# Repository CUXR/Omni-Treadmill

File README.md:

# Omni-Treadmill
A device capable of detecting motion and mimicking natural movement while keeping the users static.

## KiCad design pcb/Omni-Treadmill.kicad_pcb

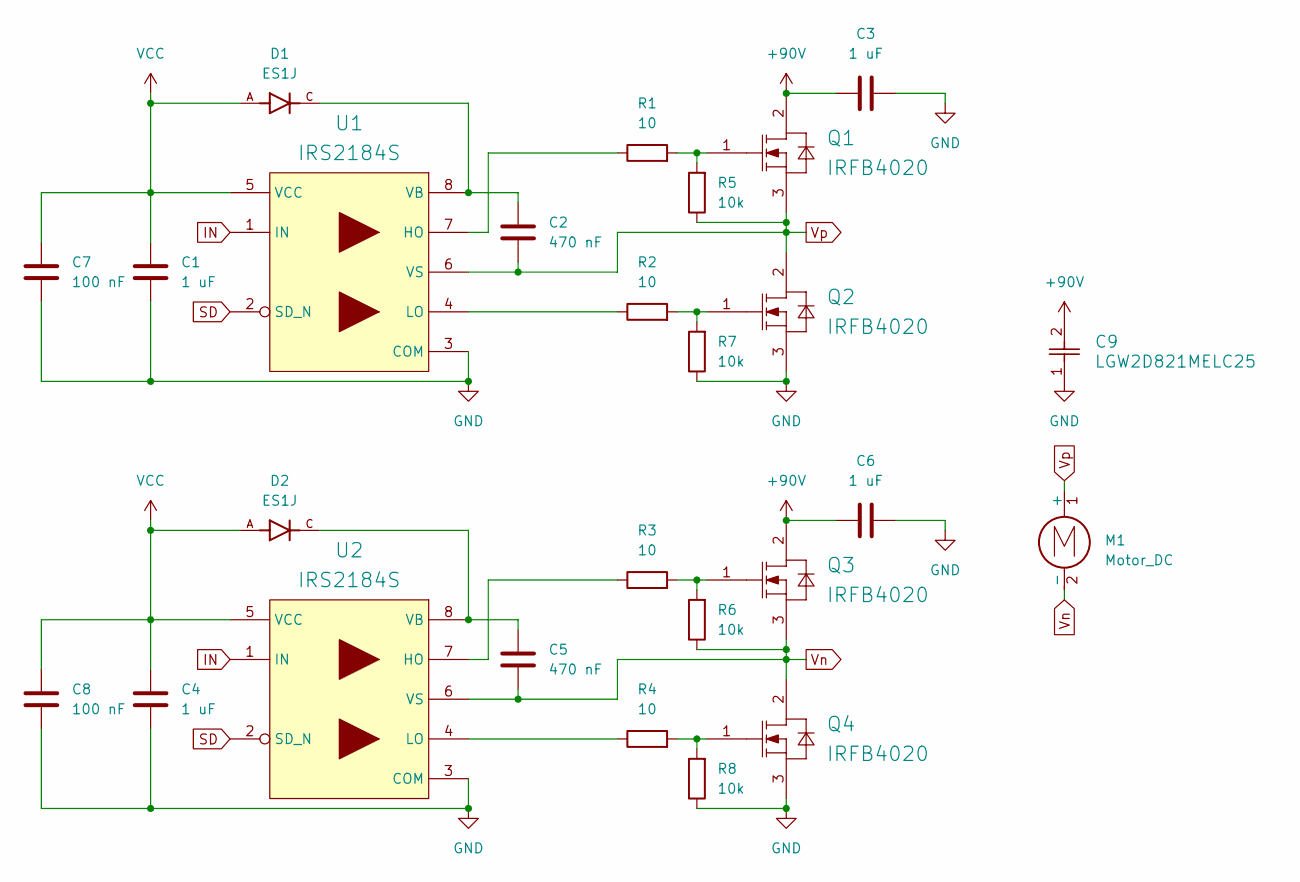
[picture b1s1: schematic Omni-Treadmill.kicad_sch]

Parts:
C1, C3, C4, C6: 1 uF; C_1812_4532Metric_Pad1.57x3.40mm_HandSolder
C2, C5: 470 nF; C_1812_4532Metric_Pad1.57x3.40mm_HandSolder
C7, C8: 100 nF; C_1206_3216Metric_Pad1.33x1.80mm_HandSolder
C9: LGW2D821MELC25; CAP_C25_NCH
D1, D2: ES1J; DIOM4325X250N; PARTREV L2102
M1: Motor_DC
Q1, Q2, Q3, Q4: IRFB4020; IFX-PG-TO220-3-904
R1, R2, R3, R4: 10; R_1206_3216Metric_Pad1.30x1.75mm_HandSolder
R5, R6, R7, R8: 10k; R_0805_2012Metric_Pad1.20x1.40mm_HandSolder
U1, U2: IRS2184S; SOIC127P600X175-8N-12-V

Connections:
+90V: C3.1, C6.1, C9.2, Q1.2 (DRAIN), Q3.2 (DRAIN)
GND: C1.1, C3.2, C4.1, C6.2, C7.2, C8.2, C9.1, Q2.3 (SOURCE), Q4.3 (SOURCE), R7.1, R8.1, U1.3 (COM), U2.3 (COM)
IN: U1.1 (IN), U2.1 (IN)
unnamed: Q1.1 (GATE), R1.2, R5.2
unnamed: Q2.1 (GATE), R2.2, R7.2
unnamed: Q3.1 (GATE), R3.2, R6.2
unnamed: Q4.1 (GATE), R4.2, R8.2
unnamed: R1.1, U1.7 (HO)
unnamed: R2.1, U1.4 (LO)
unnamed: C2.1, D1.C, U1.8 (VB)
unnamed: R3.1, U2.7 (HO)
unnamed: R4.1, U2.4 (LO)
unnamed: C5.1, D2.C, U2.8 (VB)
SD: U1.2 (SD_N), U2.2 (SD_N)
VCC: C1.2, C4.2, C7.1, C8.1, D1.A, D2.A, U1.5 (VCC), U2.5 (VCC)
Vn: C5.2, M1.2 (-), Q3.3 (SOURCE), Q4.2 (DRAIN), R6.1, U2.6 (VS)
Vp: C2.2, M1.1 (+), Q1.3 (SOURCE), Q2.2 (DRAIN), R5.1, U1.6 (VS)

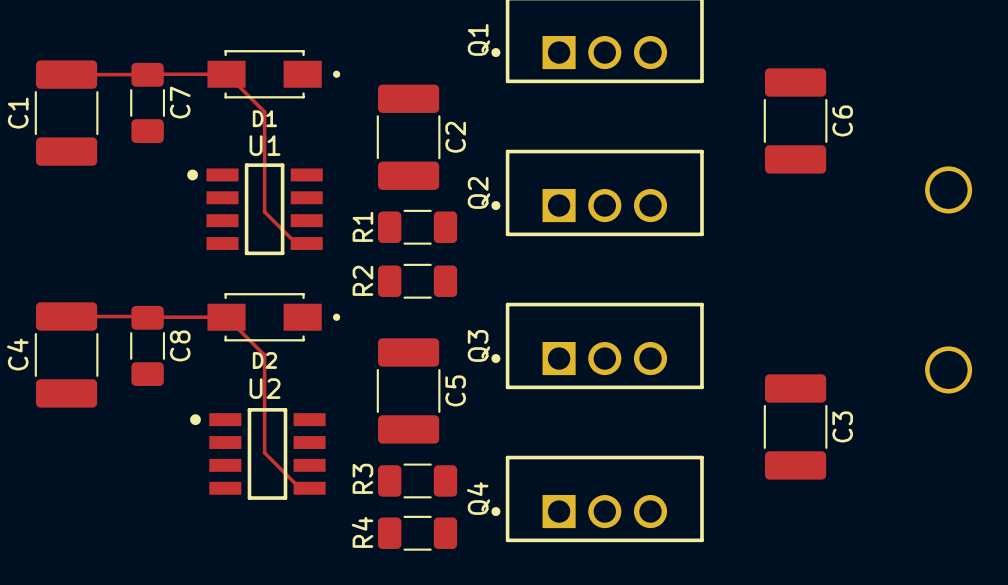
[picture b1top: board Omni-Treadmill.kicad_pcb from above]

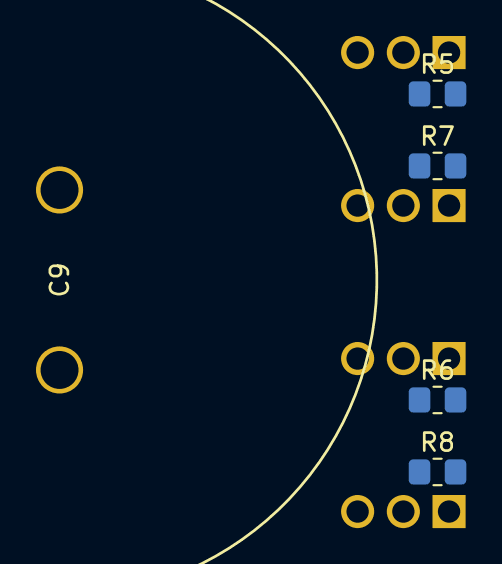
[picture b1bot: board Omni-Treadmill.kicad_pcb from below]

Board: 4 copper layers, 25 parts (5 on the bottom side), 17 nets.

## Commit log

2026-03-08 inital commit
2026-03-08 initial push
2026-03-08 Move KiCad files into pcb/ subfolder
2026-03-08 removed backups
2026-03-09 added footprints and symbols
2026-03-15 updated schematic
2026-04-09 updated hbridge and components
2026-04-15 layout complete - needs trace routing
